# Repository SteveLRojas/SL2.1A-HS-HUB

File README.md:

# SL2.1A-HS-HUB
4 port high speed USB hub

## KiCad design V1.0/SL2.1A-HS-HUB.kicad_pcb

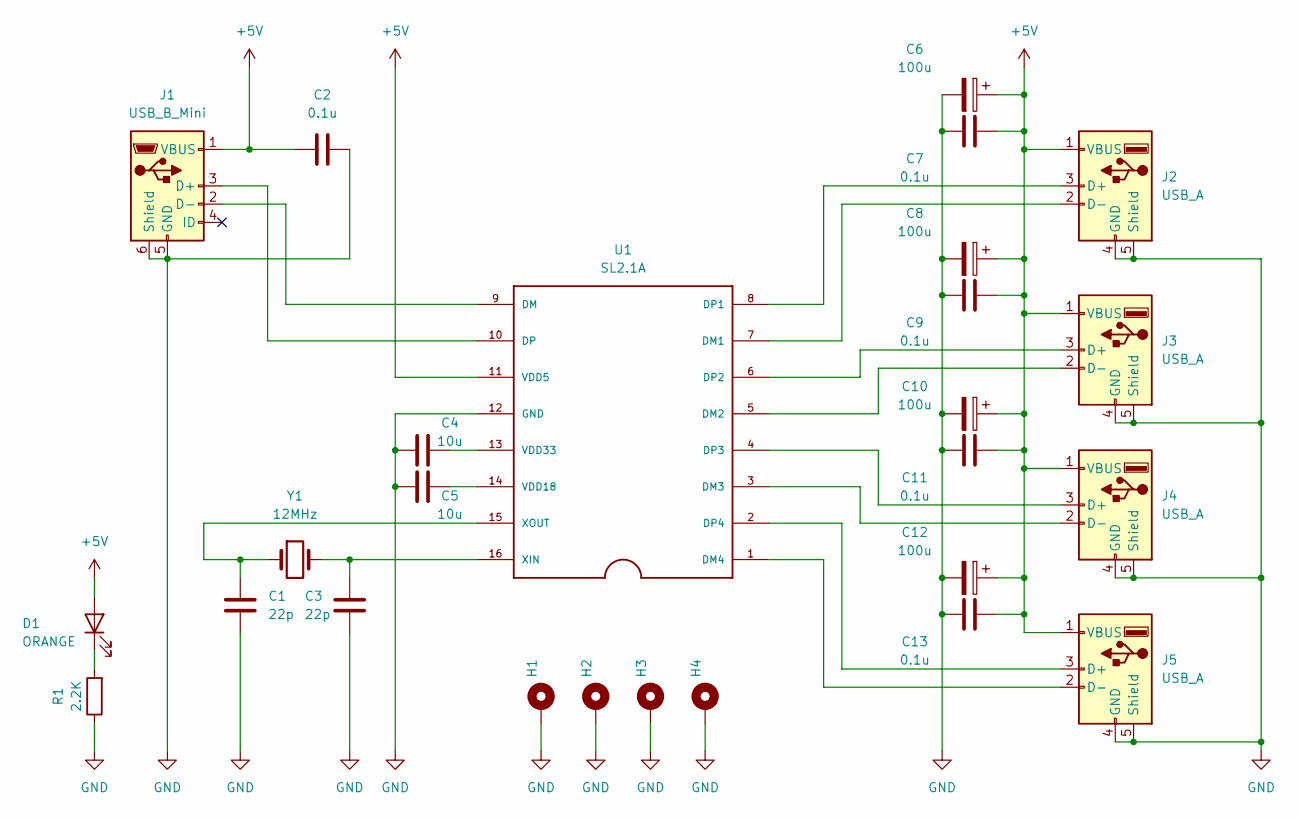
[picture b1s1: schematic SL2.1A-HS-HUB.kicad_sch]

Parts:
C1, C3: 22p; C_0805_2012Metric
C2, C7, C9, C11, C13: 0.1u; C_0805_2012Metric
C4, C5: 10u; C_1206_3216Metric
C6, C8, C10, C12: 100u; CP_Elec_6.3x5.2
D1: ORANGE; LED_0805_2012Metric
H1, H2, H3, H4: MountingHole_Pad; MountingHole_3.2mm_M3_Pad
J1: USB_B_Mini; USB_Mini-B_Wuerth_65100516121_Horizontal
J2, J3, J4, J5: USB_A; USB_A_CONNFLY_DS1095-WNR0
R1: 2.2K; R_0805_2012Metric
U1: SL2.1A; SO16
Y1: 12MHz; Crystal_HC49-4H_Vertical

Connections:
+5V: C2.1, C6.1, C7.2, C8.1, C9.2, C10.1, C11.2, C12.1, C13.2, D1.2 (A), J1.1 (VBUS), J2.1 (VBUS), J3.1 (VBUS), J4.1 (VBUS), J5.1 (VBUS), U1.11 (VDD5)
GND: C1.2, C2.2, C3.2, C4.1, C5.1, C6.2, C7.1, C8.2, C9.1, C10.2, C11.1, C12.2, C13.1, H1.1, H2.1, H3.1, H4.1, J1.5 (GND), J1.6 (Shield), J2.4 (GND), J2.5 (Shield), J3.4 (GND), J3.5 (Shield), J4.4 (GND), J4.5 (Shield), J5.4 (GND), J5.5 (Shield), R1.1, U1.12 (GND)
unnamed: C1.1, U1.15 (XOUT), Y1.1
unnamed: C3.1, U1.16 (XIN), Y1.2
unnamed: C4.2, U1.13 (VDD33)
unnamed: C5.2, U1.14 (VDD18)
unnamed: D1.1 (K), R1.2
unnamed: J1.2 (D-), U1.9 (DM)
unnamed: J1.3 (D+), U1.10 (DP)
unnamed: J2.2 (D-), U1.7 (DM1)
unnamed: J2.3 (D+), U1.8 (DP1)
unnamed: J3.2 (D-), U1.5 (DM2)
unnamed: J3.3 (D+), U1.6 (DP2)
unnamed: J4.2 (D-), U1.3 (DM3)
unnamed: J4.3 (D+), U1.4 (DP3)
unnamed: J5.2 (D-), U1.1 (DM4)
unnamed: J5.3 (D+), U1.2 (DP4)

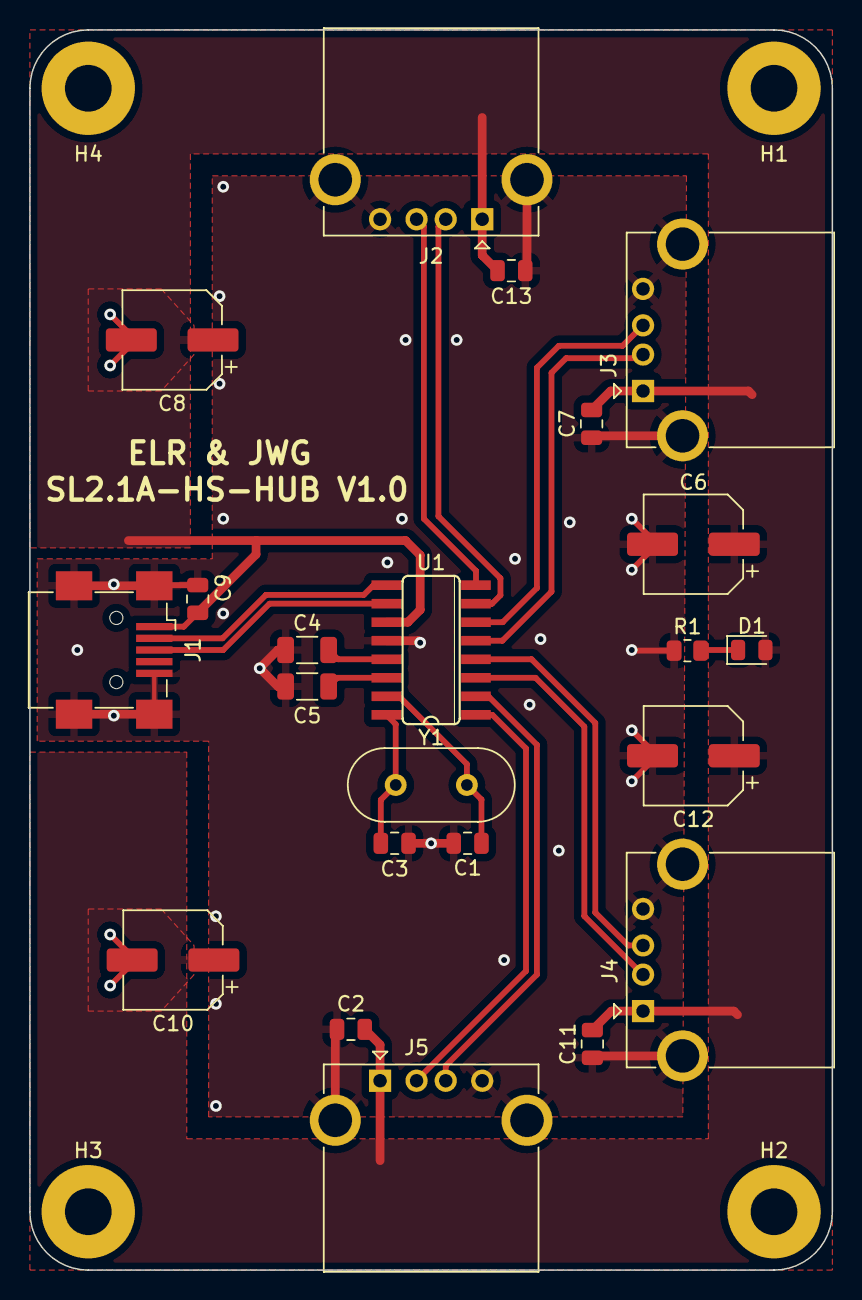
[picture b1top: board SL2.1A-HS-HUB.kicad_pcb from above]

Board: 2 copper layers, 55.0 x 85.0 mm, 26 parts (0 on the bottom side), 17 nets.

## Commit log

2024-05-10 Added V1.0 files
